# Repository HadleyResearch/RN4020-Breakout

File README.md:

# RN4020-Breakout
A simple breakout board for the Microchip RN4020 BLE Module

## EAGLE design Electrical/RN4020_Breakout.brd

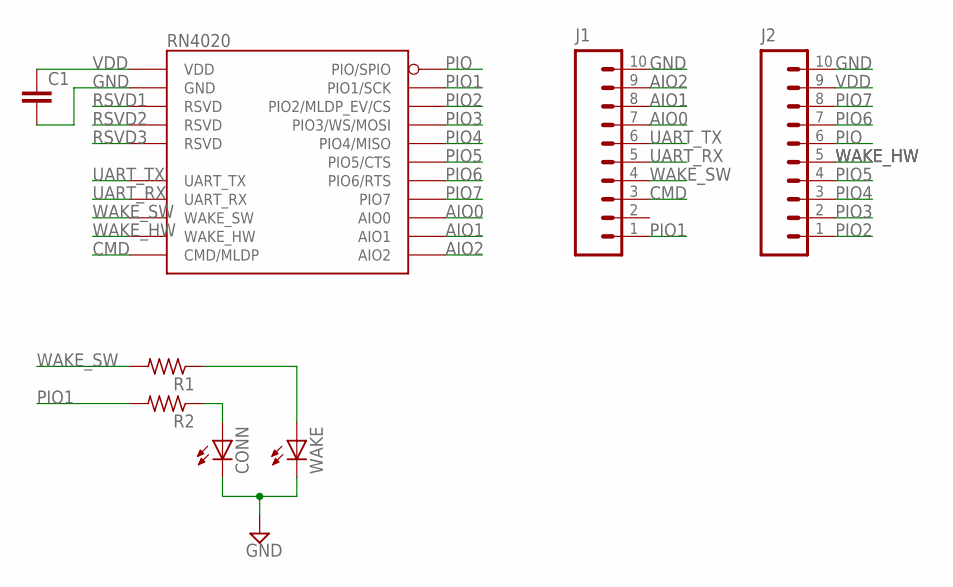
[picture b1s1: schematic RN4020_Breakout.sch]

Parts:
C1: C-EUC0805; C0805
CONN: LEDCHIPLED_0805; CHIPLED_0805
J1, J2: M10LOCK; 1X10_LOCK
R1, R2: R-US_R0805; R0805
RN4020: RN4020
WAKE: LEDCHIPLED_0805; CHIPLED_0805

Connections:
AIO0: J1.7, RN4020.P$4 (AIO0)
AIO1: J1.8, RN4020.P$3 (AIO1)
AIO2: J1.9, RN4020.P$2 (AIO2)
CMD: J1.3, RN4020.P$8 (CMD/MLDP)
GND: C1.2, CONN.C, J1.10, J2.10, RN4020.P$1 (GND), RN4020.P$9 (GND), RN4020.P$16 (GND), RN4020.P$24 (GND), WAKE.C
unnamed: R1.1, WAKE.A
unnamed: CONN.A, R2.1
PIO: J2.6, RN4020.P$17 (PIO/SPIO)
PIO1: J1.1, R2.2, RN4020.P$10 (PIO1/SCK)
PIO2: J2.1, RN4020.P$11 (PIO2/MLDP_EV/CS)
PIO3: J2.2, RN4020.P$12 (PIO3/WS/MOSI)
PIO4: J2.3, RN4020.P$13 (PIO4/MISO)
PIO5: J2.4, RN4020.P$14 (PIO5/CTS)
PIO6: J2.7, RN4020.P$18 (PIO6/RTS)
PIO7: J2.8, RN4020.P$19 (PIO7)
RSVD1: RN4020.P$20 (RSVD)
RSVD2: RN4020.P$21 (RSVD)
RSVD3: RN4020.P$22 (RSVD)
UART_RX: J1.5, RN4020.P$6 (UART_RX)
UART_TX: J1.6, RN4020.P$5 (UART_TX)
VDD: C1.1, J2.9, RN4020.P$23 (VDD)
WAKE_HW: J2.5, RN4020.P$15 (WAKE_HW)
WAKE_SW: J1.4, R1.2, RN4020.P$7 (WAKE_SW)

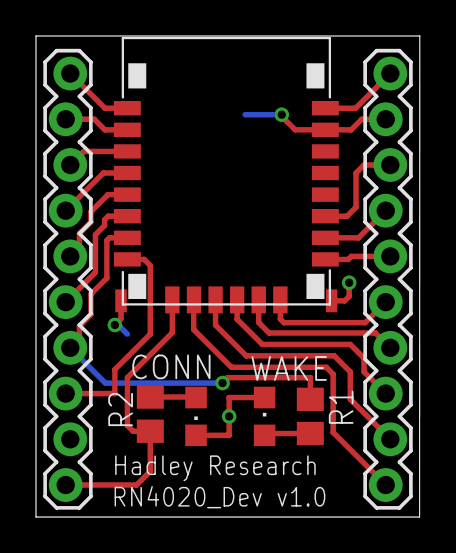
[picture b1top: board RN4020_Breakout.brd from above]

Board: 2 copper layers, 21.3 x 26.7 mm, 8 parts (1 on the bottom side), 20 nets.

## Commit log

2017-02-17 Initial commit of RN4020 breakout board

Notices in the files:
parts and their libraries:
SparkFun-Connectors: Licensing: Creative Commons ShareAlike 4.0 International - https://creativecommons.org/licenses/by-sa/4.0
